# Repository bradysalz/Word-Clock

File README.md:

# Word-Clock
MSP430 based Word Clock for my GE423 HW Project. Decided to make it more of a "word search" than a simple light up clock. Tells the time in five minute intervals. 

## Description
First thing to do is program the init script for the RTC. A backup coin cell battery will make sure it shouldn't need to be re-calibrated for another 15 years (approximate). In normal mode, the MSP430 wakes from sleep and pings the RTC approximately every minute. This occurs by doing several I2C register reads from the device. Each of the "words" (listed below) is an LED load with one LED per letter, and the entire word is turned on/off by a transistor (n-channel FET). All of the 21 words' transistor gates are driven by three 8-bit daisy-chained serial-parallel shift registers. Once the RTC data is parsed, it is converted and shifted out to light up the appropriate phrasing. 

We also have a button available on the MSP430 that will open and close shades on the front of the clock via two servo motors. I eventually plan to automate this based on a custom alarm or light sensor. 

### Words
- Minutes
    - Five
    - Ten
    - Quarter
    - Twenty
    - Half
        
+ Phrases
    + Past
    + To
    + It Is
    + O Clock

As well as the hours One through Twelve. 

### To Do
- [x] Outline letters
- [x] Design Schematic
- [x] Design PCB
- [x] Code MSP430 RTC reads
- [x] Code MSP430 shift register writes
- [ ] Code MSP430 servo drivers
- [x] Design physical enclosure
- [ ] Build physical enclosure
- [ ] Wire LEDs/resistors
- [ ] Add curtains

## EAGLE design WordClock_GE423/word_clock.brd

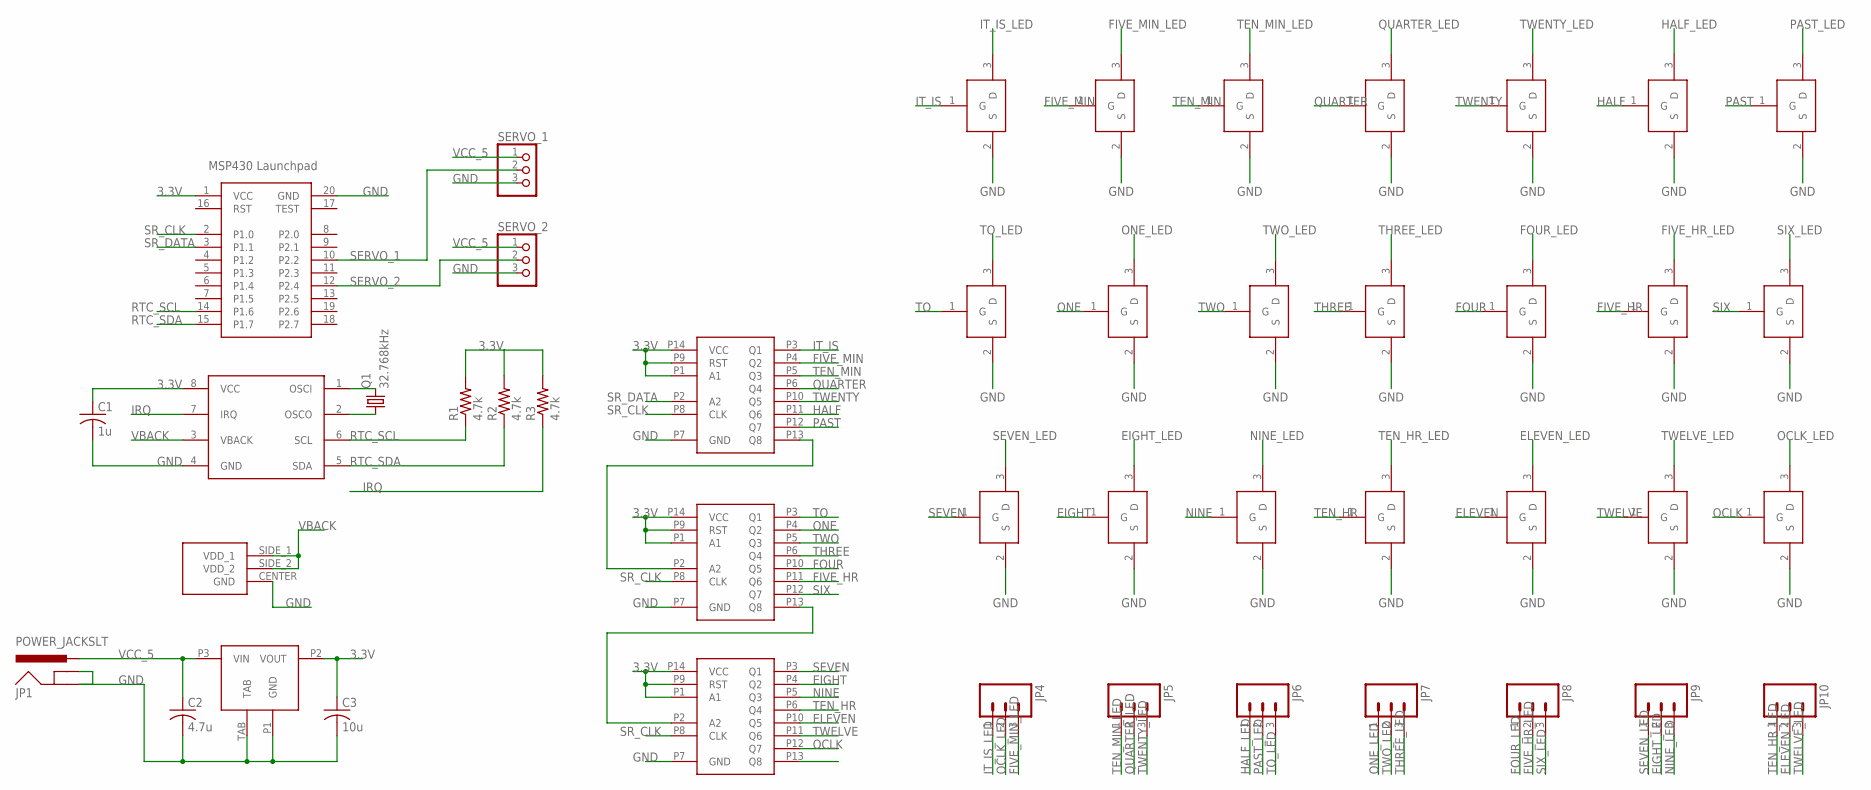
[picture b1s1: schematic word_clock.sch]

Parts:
C1: 1u; C050-025X075
C2: 4.7u; C050-025X075
C3: 10u; C050-025X075
JP1: POWER_JACKSLT; POWER_JACK_SLOT
JP4, JP5, JP6, JP7, JP8, JP9, JP10: M03-SCREW-5MM; SCREWTERMINAL-5MM-3
Q1: 32.768kHz; TC26V
R1, R2, R3: 4.7k; 0207/10
SERVO_1, SERVO_2: PINHD-1X3; 1X03
SR_1, SR_2: SHIFT_REGISTER
U$1: SHIFT_REGISTER
U$4: LDO
U$5, U$6, U$7, U$8, U$9, U$10, U$11, U$12, U$13, U$14, U$15, U$16, U$17, U$18, U$19, U$20, U$21, U$22, U$23, U$24, U$27: FET; SOT23
U$25: MSP430
U$26: RTC; SOIC8
U$28: COIN_CELL_SPARKFUN

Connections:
3.3V: C1.1, C3.1, R1.2, R2.2, R3.2, SR_1.P1 (A1), SR_1.P9 (RST), SR_1.P14 (VCC), SR_2.P1 (A1), SR_2.P9 (RST), SR_2.P14 (VCC), U$1.P1 (A1), U$1.P9 (RST), U$1.P14 (VCC), U$4.P2 (VOUT), U$25.1 (VCC), U$26.8 (VCC)
EIGHT: U$1.P4 (Q2), U$20.1 (G)
EIGHT_LED: JP9.2, U$20.3 (D)
ELEVEN: U$1.P10 (Q5), U$23.1 (G)
ELEVEN_LED: JP10.2, U$23.3 (D)
FIVE_HR: SR_2.P11 (Q6), U$17.1 (G)
FIVE_HR_LED: JP8.2, U$17.3 (D)
FIVE_MIN: SR_1.P4 (Q2), U$6.1 (G)
FIVE_MIN_LED: JP4.3, U$6.3 (D)
FOUR: SR_2.P10 (Q5), U$16.1 (G)
FOUR_LED: JP8.1, U$16.3 (D)
GND: C1.2, C2.2, C3.2, JP1.GND@1 (GNDBREAK), JP1.GND@2 (GND), SERVO_1.3, SERVO_2.3, SR_1.P7 (GND), SR_2.P7 (GND), U$1.P7 (GND), U$4.P1 (GND), U$4.TAB, U$5.2 (S), U$6.2 (S), U$7.2 (S), U$8.2 (S), U$9.2 (S), U$10.2 (S), U$11.2 (S), U$12.2 (S), U$13.2 (S), U$14.2 (S), U$15.2 (S), U$16.2 (S), U$17.2 (S), U$18.2 (S), U$19.2 (S), U$20.2 (S), U$21.2 (S), U$22.2 (S), U$23.2 (S), U$24.2 (S), U$25.20 (GND), U$26.4 (GND), U$27.2 (S), U$28.CENTER (GND)
HALF: SR_1.P11 (Q6), U$10.1 (G)
HALF_LED: JP6.1, U$10.3 (D)
IRQ: R3.1, U$26.7 (IRQ)
IT_IS: SR_1.P3 (Q1), U$5.1 (G)
IT_IS_LED: JP4.1, U$5.3 (D)
unnamed: Q1.1, U$26.2 (OSCO)
unnamed: Q1.2, U$26.1 (OSCI)
unnamed: SR_1.P13 (Q8), SR_2.P2 (A2)
unnamed: SR_2.P13 (Q8), U$1.P2 (A2)
NINE: U$1.P5 (Q3), U$21.1 (G)
NINE_LED: JP9.3, U$21.3 (D)
OCLK: U$1.P12 (Q7), U$27.1 (G)
OCLK_LED: JP4.2, U$27.3 (D)
ONE: SR_2.P4 (Q2), U$13.1 (G)
ONE_LED: JP7.1, U$13.3 (D)
PAST: SR_1.P12 (Q7), U$11.1 (G)
PAST_LED: JP6.2, U$11.3 (D)
QUARTER: SR_1.P6 (Q4), U$8.1 (G)
QUARTER_LED: JP5.2, U$8.3 (D)
RTC_SCL: R1.1, U$25.14 (P1.6), U$26.6 (SCL)
RTC_SDA: R2.1, U$25.15 (P1.7), U$26.5 (SDA)
SERVO_1: SERVO_1.2, U$25.10 (P2.2)
SERVO_2: SERVO_2.2, U$25.12 (P2.4)
SEVEN: U$1.P3 (Q1), U$19.1 (G)
SEVEN_LED: JP9.1, U$19.3 (D)
SIX: SR_2.P12 (Q7), U$18.1 (G)
SIX_LED: JP8.3, U$18.3 (D)
SR_CLK: SR_1.P8 (CLK), SR_2.P8 (CLK), U$1.P8 (CLK), U$25.2 (P1.0)
SR_DATA: SR_1.P2 (A2), U$25.3 (P1.1)
TEN_HR: U$1.P6 (Q4), U$22.1 (G)
TEN_HR_LED: JP10.1, U$22.3 (D)
TEN_MIN: SR_1.P5 (Q3), U$7.1 (G)
TEN_MIN_LED: JP5.1, U$7.3 (D)
THREE: SR_2.P6 (Q4), U$15.1 (G)
THREE_LED: JP7.3, U$15.3 (D)
TO: SR_2.P3 (Q1), U$12.1 (G)
TO_LED: JP6.3, U$12.3 (D)
TWELVE: U$1.P11 (Q6), U$24.1 (G)
TWELVE_LED: JP10.3, U$24.3 (D)
TWENTY: SR_1.P10 (Q5), U$9.1 (G)
TWENTY_LED: JP5.3, U$9.3 (D)
TWO: SR_2.P5 (Q3), U$14.1 (G)
TWO_LED: JP7.2, U$14.3 (D)
VBACK: U$26.3 (VBACK), U$28.SIDE_1 (VDD_1), U$28.SIDE_2 (VDD_2)
VCC_5: C2.1, JP1.PWR, SERVO_1.1, SERVO_2.1, U$4.P3 (VIN)

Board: 2 copper layers, 45 parts (0 on the bottom side), 57 nets, no tracks yet.

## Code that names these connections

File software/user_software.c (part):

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#include "UART.h"

// my local defns for calculating LED output
#define IT_IS    0x0000001
#define FIVE_MIN 0x0000002
#define TEN_MIN  0x0000004
#define QUARTER  0x0000008
#define TWENTY   0x0000010
#define HALF     0x0000020
#define PAST     0x0000040
#define TO       0x0000080
#define ONE      0x0000100
#define TWO      0x0000200
#define THREE    0x0000400
#define FOUR     0x0000800
#define FIVE_HR  0x0001000
#define SIX      0x0002000
#define SEVEN    0x0004000
#define EIGHT    0x0008000
#define NINE     0x0100000
#define TEN_HR   0x0200000
#define ELEVEN   0x0400000
#define TWELVE   0x0800000
#define OCLK     0x1000000

// register maps
#define REG_SECONDS 0x00
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
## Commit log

2015-03-28 :lollipop: Added .gitattributes & .gitignore files
2015-03-28 initial commit
    adding letter layout, randomize script
2015-03-28 starting eagle schematic
    added all parts to eagle schematic
2015-03-28 added eagle library
    added library i made with specific parts i used. usefulness probably
    near 0/10 but just in case
2015-03-29 initial board
    finished initial schematic
    laid out (no routing) first board
2015-03-29 added DRC
    oshpark's DRC
2015-03-29 updated gitignore
    stupid eaglecad with stupid reversion saving
2015-03-29 finished boards
    finally. added VCC rail for LEDs
2015-03-29 added picture form
    yay colors
2015-03-29 fixed pcb picture
    definitely didn't upload 2 pics as .sch
2015-03-29 deleted temp files
2015-03-29 made readme
    wow that todo list is long yikes
2015-03-29 renamed directory
    changed to hardware to make it prettier 4 kashev
2015-03-29 created msp430 skeleton
    thanks to dan block for the general skeleton code with basic
    main/interrupts/UART
2015-03-29 cleaning up
2015-03-29 still cleaning up
2015-03-31 added STL file
    first iteration
2015-04-01 update readme
    fixed checkboxes
2015-04-08 moved config code out of main loop
2015-04-08 remove extra interrupt UART
2015-04-08 remove old GPIO config
2015-04-08 add clock pulse
2015-04-16 demo I2C code
    thanks dan block
2015-04-16 random CCS stuff
    lol what is eclipse
2015-04-16 adding register maps
2015-04-16 more I2C config
2015-04-16 added idle function
2015-04-16 adding setRegister function
2015-04-16 clean up changes
2015-04-16 added getRegister function
2015-04-16 initial calibration
2015-04-16 more definitions
2015-04-16 initial control flow
2015-04-16 calibrate function
2015-04-16 minutes parsing
2015-04-16 hour parsing
2015-04-16 moved current time comments
2015-04-16 shift data functionality
2015-04-16 readme doe
2015-04-16 tabs to spaces
2015-04-16 clean up
2015-04-16 just testing to see if it builds
2015-04-21 yay it builds
2015-04-21 moved ugly if/else/switch code to function
2015-04-21 adding servocode
2015-04-21 added spare code for demo
2015-04-21 printf debugging

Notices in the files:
parts and their libraries:
SparkFun-Connectors: Licensing: Creative Commons ShareAlike 4.0 International - https://creativecommons.org/licenses/by-sa/4.0
